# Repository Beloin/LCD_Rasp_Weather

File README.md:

# Weather Station with Raspberry PI Zero 2W

In this project was implemented a simple Temperature and Humidity station using Raspberry PI Zero 2W, an LCD and DHT11.

In order to run both in Linux system and Raspberry PI, it was created conditional compilation
explicit in [Code Structure](#Code-Structure) and implemented in `PeripheralFactory`. So while using Linux
is used the `ConsoleDisplay` implementation, and in RPI0 is used `LCDDisplay`. Also, to have the Weather
data is implemented `RandomWeatherGeneratorTask` and in RPI0 `DHT11Sensor`.

The program uses mean 7%CPU in the RaspOS - Raspberry PI Zero 2W. Could use less if implemented time
interruptions to some delays.

<div style="display: grid; grid-template-columns: 1fr 1fr 1fr; column-gap: 20px; place-items: center;">
    
</div>

## Dependencies

- [pigpio](http://abyz.me.uk/rpi/pigpio/cif.html) (Usually comes pre-installed on pi boards)
- pthreads: `sudo apt-get install libpthread-stubs0-dev`
    - Make DHT11 Workers.
- spdlog: `pacman -S spdlog` or in apt based system `sudo apt install libspdlog-dev`
    - Simple and Fast Logging Library

## Schematics

<div style="display: grid; grid-template-columns: 1fr 1fr 1fr; column-gap: 20px; place-items: center;">
    
</div>

## Circuit

<div style="display: grid; grid-template-columns: 1fr 1fr 1fr; column-gap: 20px; place-items: center;">
    
</div>

# Code Structure

### Display

There's an `interface` that dictates the way all the data will be set on display: the `TextBasedDisplay`

<div style="display: grid; grid-template-columns: 1fr 1fr 1fr; column-gap: 20px; place-items: center;">
    
</div>

### WeatherStatusTask

There's an `interface` that dictates the way the weather is acquired. The data will be scoped in a single
struct named `WeatherInfo`. The `WeatherTask` will be running in its own thread, acquiring the data and writing it to
the `WeatherInfo` struct. Race conditions are not treated since the program will be running in a controlled system.

<div style="display: grid; grid-template-columns: 1fr 1fr 1fr; column-gap: 20px; place-items: center;">
    
</div>

## References

- [Controle de GPIO da Raspberry Pi utilizando a linguagem C](https://embarcados.com.br/gpio-da-raspberry-pi-linguagem-c/)
- [bcm2835](http://www.airspayce.com/mikem/bcm2835/)
- [pigpio](http://abyz.me.uk/rpi/pigpio/index.html)

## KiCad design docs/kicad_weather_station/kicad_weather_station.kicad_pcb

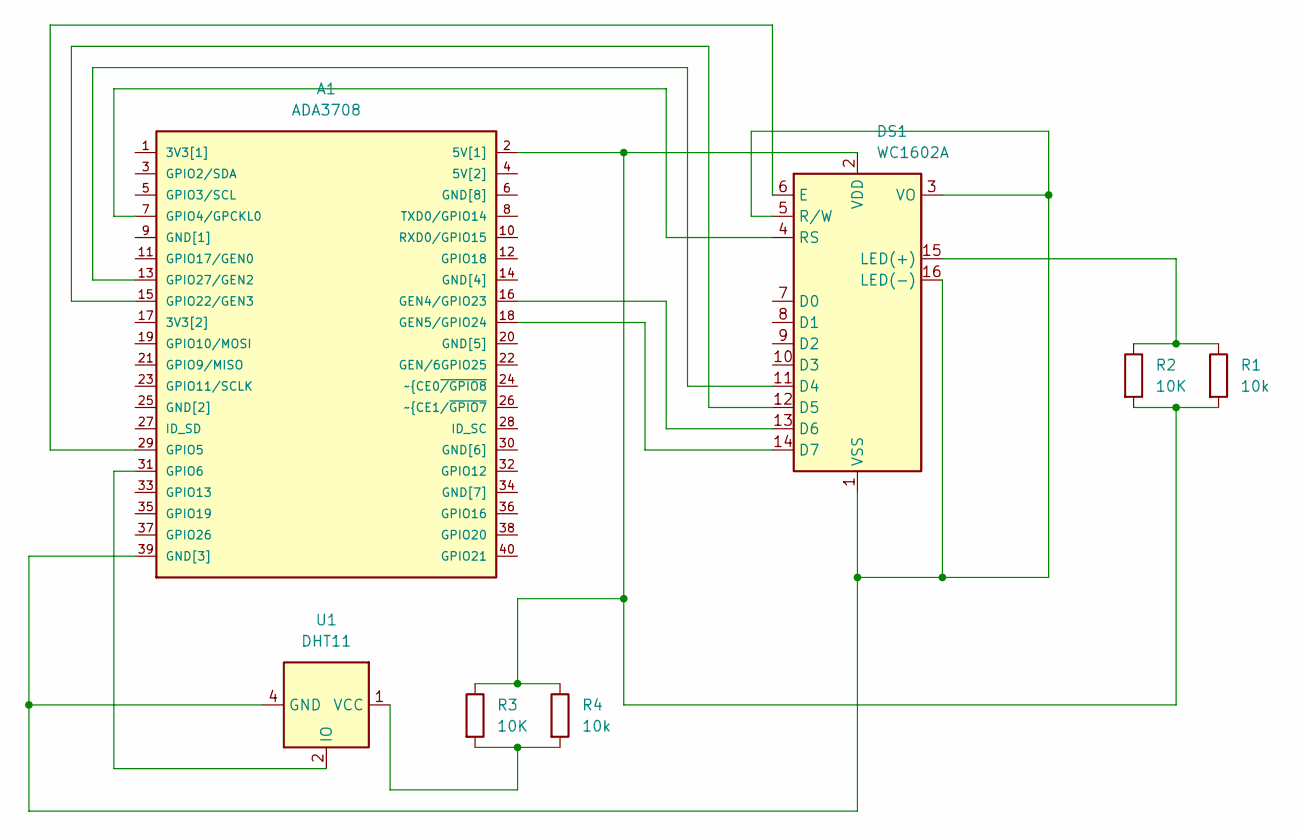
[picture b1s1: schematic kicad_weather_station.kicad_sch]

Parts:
A1: ADA3708; ADA3708_RPI-ZERO
DS1: WC1602A
R1, R4: 10k; R_0402_1005Metric
R2, R3: 10K; R_0402_1005Metric
U1: DHT11; Aosong_DHT11_5.5x12.0_P2.54mm

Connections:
unnamed: A1.2 (5V[1]), DS1.2 (VDD), R1.2, R2.2, R3.1, R4.1
unnamed: A1.16 (GEN4/GPIO23), DS1.13 (D6)
unnamed: A1.18 (GEN5/GPIO24), DS1.14 (D7)
unnamed: A1.39 (GND[3]), DS1.1 (VSS), DS1.3 (VO), DS1.5 (R/W), DS1.16 (LED(-)), U1.4 (GND)
unnamed: A1.7 (GPIO4/GPCKL0), DS1.4 (RS)
unnamed: A1.29 (GPIO5), DS1.6 (E)
unnamed: A1.31 (GPIO6), U1.2 (IO)
unnamed: A1.15 (GPIO22/GEN3), DS1.12 (D5)
unnamed: A1.13 (GPIO27/GEN2), DS1.11 (D4)
unnamed: DS1.15 (LED(+)), R1.1, R2.1
unnamed: R3.2, R4.2, U1.1 (VCC)

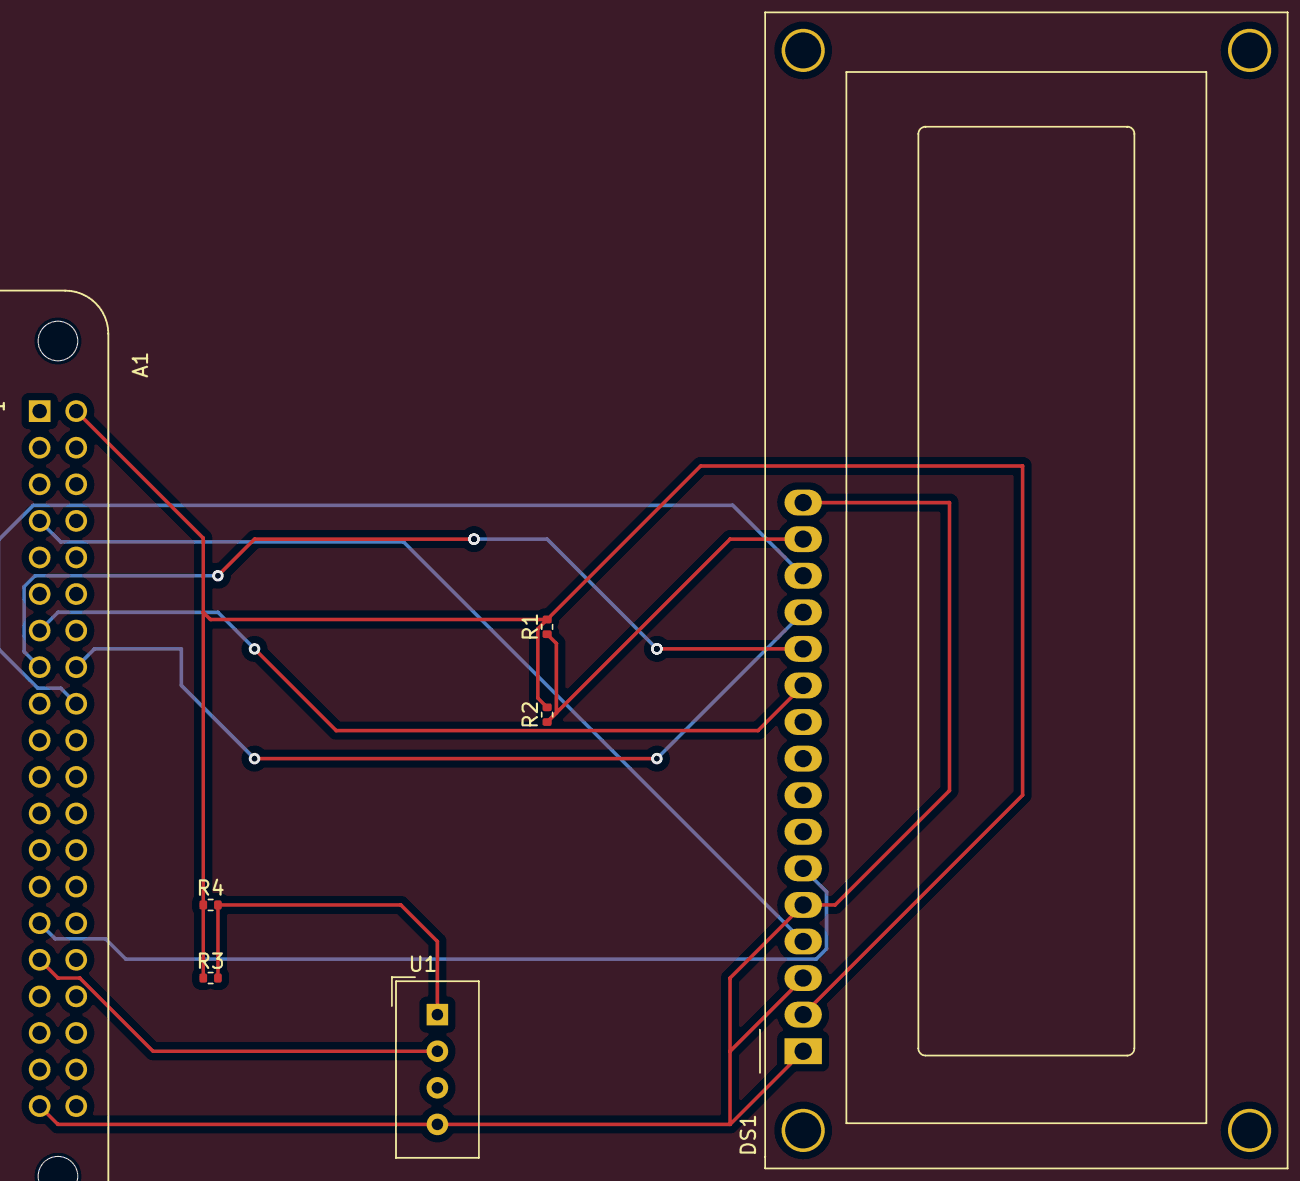
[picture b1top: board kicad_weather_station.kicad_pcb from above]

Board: 2 copper layers, 7 parts (0 on the bottom side), 11 nets.

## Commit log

2023-08-01 Updated .gitignore
2023-08-01 Initial Commit: Created CMakeLists.txt for project and tests
2023-08-05 Creating docs
2023-08-06 Fisrt creating how i think the implementations will be defined
2023-08-06 Using new directory structure in include and libs
2023-08-06 Now using cmake to tell which implementations the program will use
2023-08-19 Updated CMakeList.txt structure
2023-09-16 Using default pigpio to raise led
2023-09-20 Added pigpio to librarie
2023-09-22 Added pigpio header to get types
2023-09-24 Using namespace Display in All display info
2023-09-24 Fixing namspaces
2023-09-24 Using PeripheralFactory
2023-09-24 Using WeatherStatus as a Task instead of only function
2023-09-24 Implementing DHT11 fisrt so we can weld female pins to LCD
2023-09-24 Implementing DHT11
2023-09-24 Testing DHT11 implementation
2023-09-24 WIP: DHT11 Sensor
2023-09-24 Removing build files
2023-09-24 Adding ingore to vuild files
2023-10-12 Using Pthreads
2023-10-12 Removed all build and debug itens
2023-10-12 Using spdlog to add logs
2023-10-12 Renamed Method naming Convetion
2023-10-12 Created LCD.. Now we need to test
2023-10-12 Updated ShowText
2023-10-12 Usng Static works?
2023-10-12 Updated where initialization is
2023-10-12 Added debug prints
2023-10-12 Added pigpio.h to PeripheralFactory
2023-10-12 Updarted console
2023-10-12 Reading the docs always helps
2023-10-12 Testing somethings
2023-10-12 Removed delays
2023-10-12 Using real data
2023-10-12 Removed big delays
2023-10-13 Adding Temeprature and Weather Task
2023-10-13 Better Logs
2023-10-13 Done everythiong working... Allways check your DDP
2023-10-13 Updating data representation
2023-10-14 Updated README.md and updated parseString code
2023-10-14 Updated README.md and schematics
2023-10-14 Added Image on docs]
2023-10-14 Added Image on docs
